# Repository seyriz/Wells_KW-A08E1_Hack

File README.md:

# Wells KW-A08E1 공기청정기 핵
이 프로젝트는 교원웰스의 KW-A08E1 공기청정기의 기능을 해킹해서 인터넷에 접속된 IoT 공기청정기로 만드는 프로젝트입니다.

# 프로젝트의 목표
일반 공기청정기를 미세먼지, TVOCs, 온/습도 측정기능 및 그에따른 공기청정기능을 하면서 인터넷을 이용해 원격지에서 관측 및 제어를 할 수 있는 IoT 공기청정기로 개조합니다.

## 사용될 부품
| 품명 | 개수 | 설명 |
| --- | --- | --- |
| ESP-WROOM-32 | 1 | ESP32 WiFi/BT combo SoC module |
| KN2222 | 2 | General purpose NPN Transister |
| LED | 4 | 3Pi LED Thru hole, 고휘도, 백색, 적생, 녹색, 청색 각 1개 |

# CAUTION AND DISCLAIMER
이 프로젝트는 인체에 해로울 정도의 전압/전류/열량의 전기기기를 다루고 있습니다. 

이 프로젝트를 사용함에 따른 불가역적인 기기의 손상, 보증의 무효화, 부상, 사망은 모두 사용자의 책임입니다.

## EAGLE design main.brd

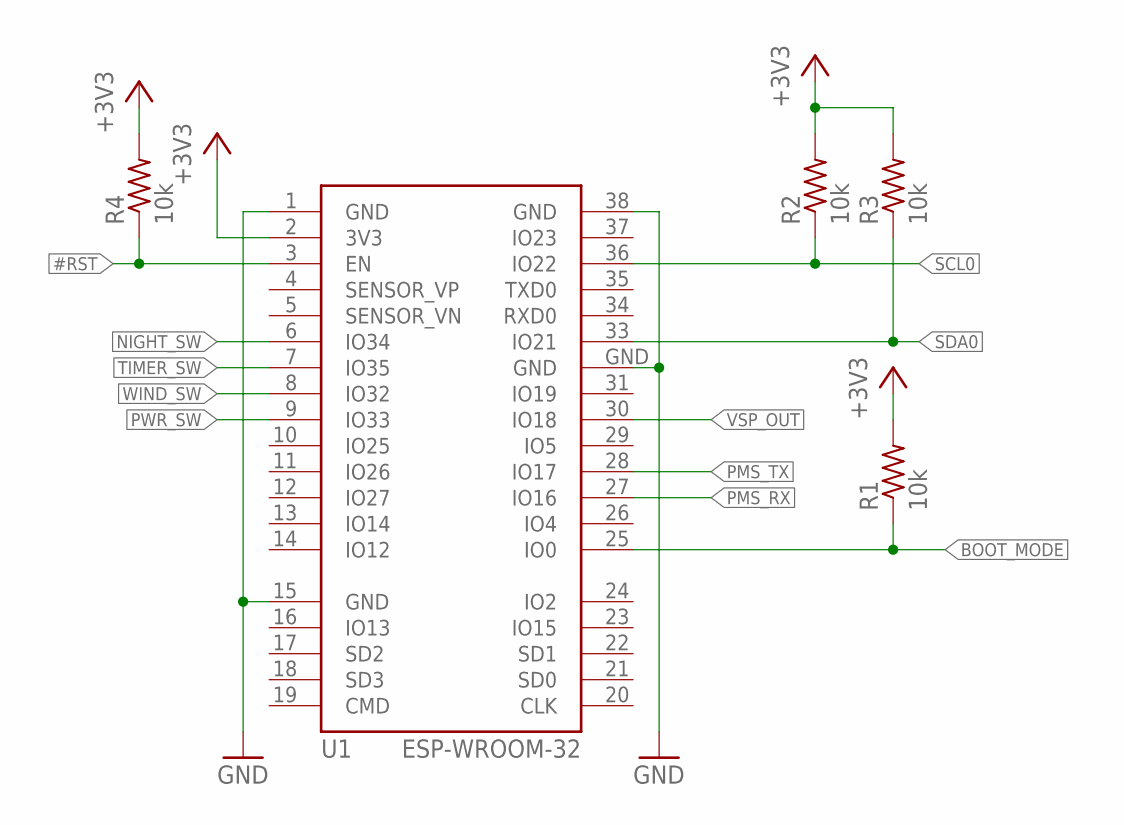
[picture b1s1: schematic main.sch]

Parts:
R1, R2, R3, R4: 10k; R0603
U1: ESP-WROOM-32

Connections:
#RST: R4.1, U1.3 (EN)
+3V3: R1.2, R2.2, R3.2, R4.2, U1.2 (3V3)
BOOT_MODE: R1.1, U1.25 (IO0)
GND: U1.1 (GND), U1.15 (GND), U1.38 (GND), U1.GND
NIGHT_SW: U1.6 (IO34)
PMS_RX: U1.27 (IO16)
PMS_TX: U1.28 (IO17)
PWR_SW: U1.9 (IO33)
SCL0: R2.1, U1.36 (IO22)
SDA0: R3.1, U1.33 (IO21)
TIMER_SW: U1.7 (IO35)
VSP_OUT: U1.30 (IO18)
WIND_SW: U1.8 (IO32)

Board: 2 copper layers, 5 parts (0 on the bottom side), 6 nets, no tracks yet.

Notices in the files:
parts and their libraries:
esp32: Creative Commons Attribution-ShareAlike 4.0 International
